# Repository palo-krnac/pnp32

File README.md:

# 🎯 **pnp32 Modular Motion Controller for openPNP**

High-performance, fully modular motion controller for advanced Pick & Place machines. Designed to seamlessly integrate with OpenPnP and support direct SPI-controlled stepper drivers for ultra-smooth and precise motion.

!!! danger "Work in Progress"
    This project is currently under active development.  
    Features and documentation may change frequently.  
    Use at your own discretion.

👉 [See pnp32 documentation page](https://pnp32.telemetry.digital)

---

## 🚀 **Key Features**

- ✅ **ESP32 based core** — powerful microcontroller with floating-point, high-speed I/O, and robust connectivity
- ✅ **Native SPI motion control** — supports TMC5160, TMC5130, PowerSTEP01, and L64xx drivers without STEP/DIR emulation
- ✅ **Flexible architecture** — single-board and multi-board configurations for scalable machine designs
- ✅ **CAN bus interface** — robust communication between multiple controllers or modular head units
- ✅ **RS485 interface** — control feeder modules or additional peripherals with industrial reliability
- ✅ **Integrated vacuum and air control** — including pressure/vacuum sensing and smart valve control
- ✅ **Advanced lighting and vision control** — supports multi-channel LED lighting, camera triggers, and auxiliary outputs
- ✅ **USB-to-Serial bridge** — direct communication with OpenPnP software

---

## 🧩 **Modifications & Configurations**

### 🔹 **Modification 1: Single Board Setup**

- All stepper motor drivers for all axes integrated on one board
- Centralized control logic with all communication interfaces (CAN, RS485, USB)
- Simplified wiring for smaller or simpler machines

### 🔹 **Modification 2: Dual Board Modular Setup**

#### 🟦 **Main Controller Board**

- Controls primary machine axes: X, Y, or duplicated X + single Y (up to 3 axes)
- Handles all communication interfaces (CAN, RS485, USB)
- Acts as the master motion controller

#### 🟩 **Head Controller Board**

- Mounted on the machine head(s), connected via CAN bus
- Controls additional axes: Z, A, B, C, D, E, F
- Supports air/vacuum control, pressure/vacuum sensing
- Controls head lighting, glue/paste dispensers
- Available in two variants:
  - 2-head version: for two nozzles
  - 4-head version: supports four nozzles or combination of nozzles & dispensers

---

## ⚙️ **G-code Configuration & Machine Parameters**

All key motion parameters and hardware configurations are set directly from OpenPnP via custom G-code commands. This enables easy tuning, calibration, and reconfiguration without modifying firmware or recompiling code.

### 💬 **Supported G-code Commands**

| G-code        | Description                                 | Example Usage                        | Documentation |
|---------------|---------------------------------------------|-------------------------------------|---------------|
| `M350`        | Set microstepping for each axis            | `M350 X16 Y16 Z32`                 | [RepRap M350](https://marlinfw.org/docs/gcode/M350.html) |
| `M906`        | Set motor current (mA) per axis           | `M906 X1000 Y1000 Z800`           | [RepRap M906](https://marlinfw.org/docs/gcode/M906.html) |
| `M92`         | Set steps per mm (axis scaling)           | `M92 X80 Y80 Z400`                | [RepRap M92](https://marlinfw.org/docs/gcode/M092.html) |
| `M211`        | Enable/disable software endstops          | `M211 S1`                          | [RepRap M211](https://marlinfw.org/docs/gcode/M211.html) |
| `M208`        | Set axis travel limits (soft limits)      | `M208 X0:300 Y0:250 Z0:150`      | [Duet3D M208](https://docs.duet3d.com/User_manual/Reference/Gcode#m208) |
| `M569`        | Configure driver direction inversion      | `M569 X0 Y1 Z0`                   | [Duet3D M569](https://docs.duet3d.com/User_manual/Reference/Gcode#m569) |
| `M912`        | Set driver sense resistor calibration     | `M912 X20 Y20 Z18`               | Custom command |
| `M913`        | Set dynamic current scaling %            | `M913 X70 Y70 Z80`              | [Duet3D M913](https://docs.duet3d.com/User_manual/Reference/Gcode#m913) |
| `M950`        | Configure pin assignments for outputs    | `M950 P1 S0`                     | [Duet3D M950](https://docs.duet3d.com/User_manual/Reference/Gcode#m950) |
| `M355`        | Control LED lighting intensity            | `M355 P1 S255`                  | [RepRap M355](https://marlinfw.org/docs/gcode/M355.html) |
| `M420`        | Enable bed leveling or machine compensation (if used) | `M420 S1`          | [RepRap M420](https://marlinfw.org/docs/gcode/M420.html) |

### 🛠 **Possible Additional Configurations**

- Set acceleration, max speed, and jerk per axis (future extension)
- Configure vacuum thresholds and pressure sensor calibration
- Assign specific CAN node IDs for multi-board setups
- Control glue/paste pump parameters (pulse lengths, flow rates)
- Define custom tool offsets and head calibration parameters

---

## 🛠 **Board Parameters**

| Parameter         | Value                                      |
|-------------------|--------------------------------------------|
| **MCU**           | ESP32                                      |
| **Motor Drivers** | SPI controlled: TMC5160, TMC5130, PowerSTEP01, L64xx |
| **Axes**          | Up to 12 axes total (depending on config) |
| **Feeders**       | Up to 63 feeders total (depending on config) |
| **Comm. Interfaces** | CAN bus, RS485, USB-Serial             |
| **Peripheral Control** | Air/vacuum valves, pressure sensors, lighting |
| **Voltage**       | 12–48 V supply for motors                |
| **Safety**        | E-stop input, software limits, watchdog  |

---

## 💻 **Software**

- Developed in **PlatformIO**
- Custom motion control firmware optimized for SPI-based drivers
- CAN bus stack for modular multi-board communication
- Feeder and peripheral control via RS485
- OpenPnP-compatible serial communication with dynamic G-code support

---

## 💡 **Highlights**

- Ultra-precise motion with direct register-level SPI control (no missed steps)
- Full machine configuration and tuning via standard G-code from OpenPnP
- Modular design ready for scalable, high-end Pick & Place machines
- Multi-head and multi-function ready: placement, glue dispensing, paste dispensing
- Designed for tinkerers, prosumers, and professional machine builders alike

---

## 📦 **Getting Started**

1️⃣ Clone this repository  
2️⃣ Install PlatformIO and dependencies  
3️⃣ Configure your hardware via G-code or `config.h` for base defaults  
4️⃣ Flash the firmware to your controller board  
5️⃣ Connect to OpenPnP and start tuning!

---

## 🛡 **License**

This project is open-source under the MIT License. Contributions and pull requests are warmly welcome!

---

## ❤️ **Credits & Inspiration**

Inspired by OpenPnP community, modern motion control concepts, and the open hardware spirit. Special thanks to Trinamic (TMC), STMicroelectronics (PowerSTEP01, L64xx), and the global DIY PnP community.

---

## ✨ **Screenshots & Diagrams**

*(Insert board design images, modular connection diagrams, example machine setups, head modules, etc.)*

---

### ✅ **Ready to go? Let's build next-level OpenPnP machines together!**
"""

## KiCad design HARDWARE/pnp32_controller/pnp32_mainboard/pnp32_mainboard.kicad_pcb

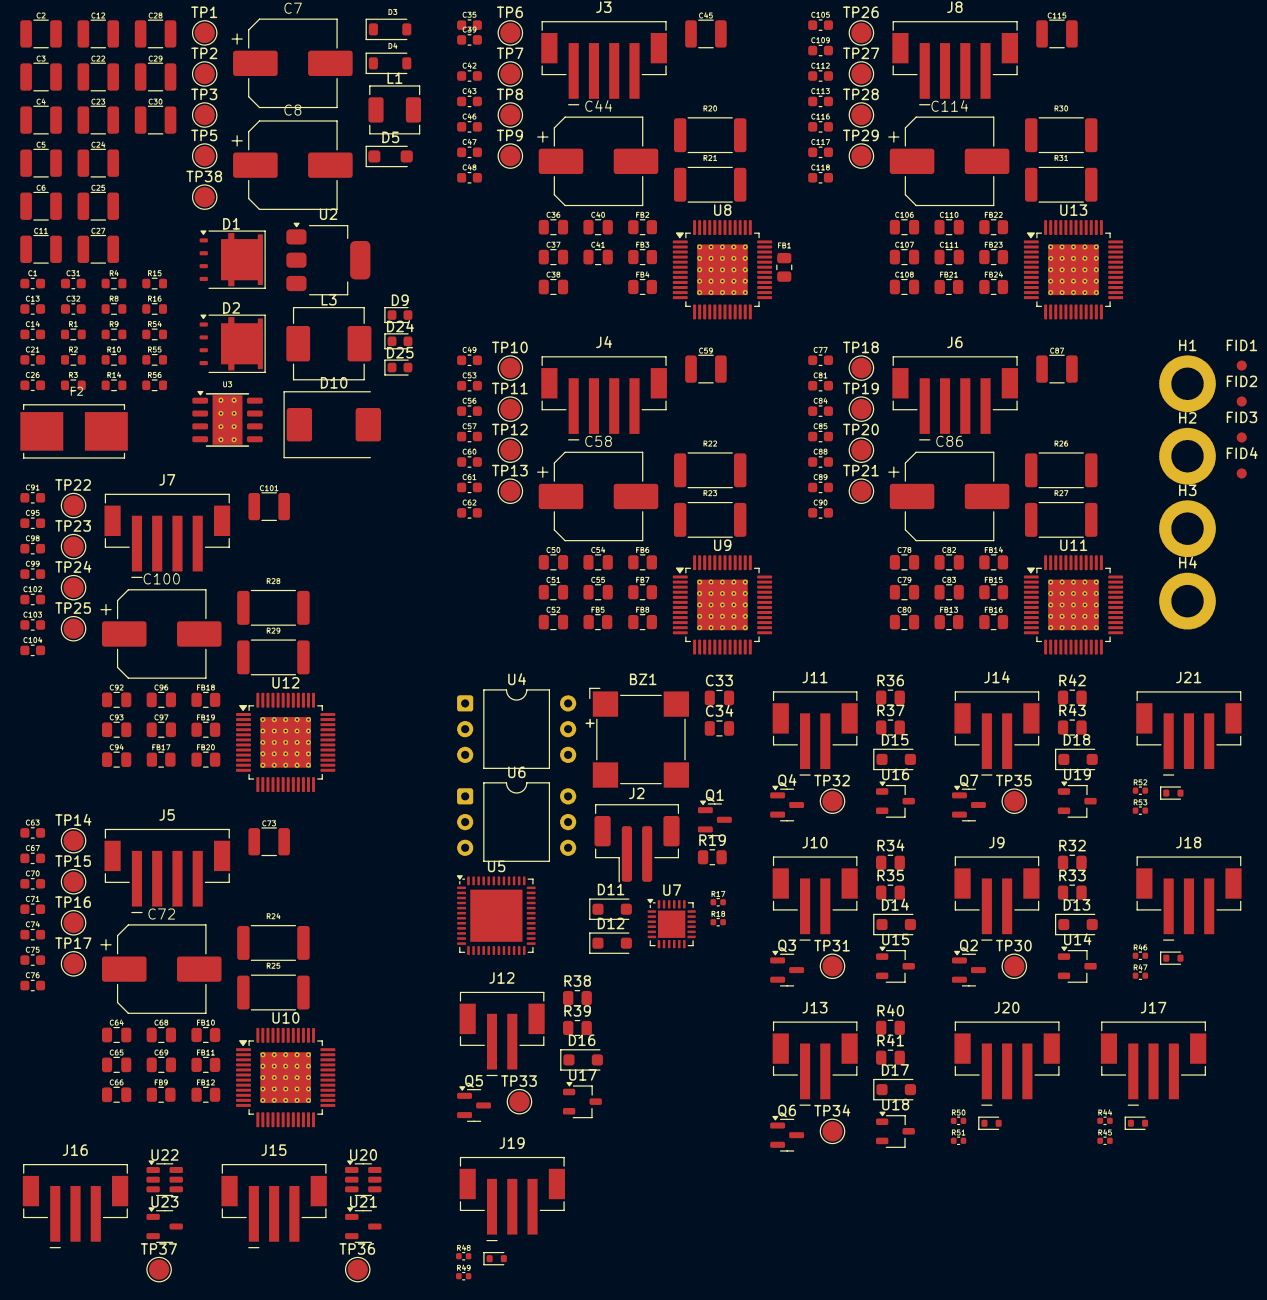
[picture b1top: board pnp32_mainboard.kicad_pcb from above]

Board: 2 copper layers, 304 parts (0 on the bottom side), 144 nets, no tracks yet.

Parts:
BZ1: Buzzer; MagneticBuzzer_CUI_CMT-8504-100-SMT
C1, C13, C14, C21, C26, C42, C43, C46, C47, C48, C56, C57, C60, C61, C62, C70, C71, C74, C75, C76, C84, C85, C88, C89, C90, C98, C99, C102, C103, C104, C112, C113, C116, C117, C118: 100nF; C_0603
C2, C3, C4, C5, C6, C11, C12, C22, C23, C24, C25, C45, C59, C73, C87, C101, C115: 10uF; C_1210
C7, C8, C44, C58, C72, C86, C100, C114: 100uF/50V; CP_Elec_8x10.5
C27, C28, C29, C30: 22uF; C_1210
C31: 47pF; C_0603
C32: 4.7nF; C_0603
C33, C34: 100n; C_0805_2012Metric
C35, C49, C63, C77, C91, C105: 4.7uF; C_0603
C36, C37, C38, C40, C41, C50, C51, C52, C54, C55, C64, C65, C66, C68, C69, C78, C79, C80, C82, C83, C92, C93, C94, C96, C97, C106, C107, C108, C110, C111: 470pF; C_0805
C39, C53, C67, C81, C95, C109: 22nF; C_0603
D1, D2: SQJ479EP-T1_GE3; PowerPAK_SO-8L_Single
D3, D4: BZT52C16; SOD-123
D5: SMF28A; SOD-123FL
D9, D24, D25: GREEN; LED_0603_1608Metric
D10: B560C; SMC
D11, D12, D13, D14, D15, D16, D17, D18: SM4007; D_SOD-123F
D19, D20, D21, D22, D23: LESD5D5.0CT1G; SOD-523
F2: 01550900M; Fuseholder_Littelfuse_Nano2_154x
FB1, FB2, FB3, FB4, FB5, FB6, FB7, FB8, FB9, FB10, FB11, FB12, FB13, FB14, FB15, FB16, FB17, FB18, FB19, FB20, FB21, FB22, FB23, FB24: FerriteBead; R_0805
FID1, FID2, FID3, FID4: Fiducial; Fiducial_1mm_Mask2mm
H1, H2, H3, H4: MountingHole_Pad; MountingHole_3.2mm_M3_DIN965_Pad
J2: FAN; JST_PH_B2B-PH-SM4-TB_1x02-1MP_P2.00mm_Vertical
J3, J4, J5, J6, J7, J8: Conn_01x04_Pin; WE_620304124022
J9, J10, J11, J12, J13, J14: Conn_01x02_Pin; WE_620302124022
J15, J16, J17, J18, J19, J20, J21: Conn_01x03_Pin; WE_620303124022
L1: 2.2uH; L_Sunlord_MWSA0402S
L3: 8.2uH; L_Changjiang_FXL0630
Q1, Q2, Q3, Q4, Q5, Q6, Q7: AO3400A; SOT-23
R1, R2, R9: 4.7kΩ; R_0603
R3, R4, R10: 10kΩ; R_0603
R8: 1kΩ; R_0603
R14: 53.6kΩ; R_0603
R15: 16.9kΩ; R_0603
R16: 243kΩ; R_0603
R17, R18: 4.7kΩ; R_0402
R19, R32, R34, R36, R38, R40, R42: 1k; R_0805_2012Metric
R20, R21, R22, R23, R24, R25, R26, R27, R28, R29, R30, R31: 120mΩ; R_2512
R33, R35, R37, R39, R41, R43: 10k; R_0805_2012Metric
R44, R46, R48, R50, R52: 10kΩ; R_0402
R45, R47, R49, R51, R53: 1kΩ; R_0402
R54: 442kΩ; R_0603
R55: 90.9kΩ; R_0603
R56: 10.2kΩ; R_0603
TP1, TP2, TP3, TP5, TP6, TP7, TP8, TP9, TP10, TP11, TP12, TP13, TP14, TP15, TP16, TP17, TP18, TP19, TP20, TP21, TP22, TP23, TP24, TP25, TP26, TP27, TP28, TP29, TP30, TP31, TP32, TP33, TP34, TP35, TP36, TP37, TP38: TestPoint; TestPoint_Pad_D2.0mm
U2: AMS1117-3.3; SOT-223
U3: TPS54560BDDAR; Texas_HSOP-8-1EP_3.9x4.9mm_P1.27mm_ThermalVias
U4, U6: XGZP6857D; DIP-6_W10.16mm
U5: ESP32-PICO-V3; QFN-48-1EP_7x7mm_P0.5mm_EP5.15x5.15mm
U7: FE1.1S-BQFN24B; WQFN-24-1EP_4x4mm_P0.5mm_EP2.7x2.7mm
U8, U9, U10, U11, U12, U13: TMC5130A-TA; TQFP-48-1EP_7x7mm_P0.5mm_EP5x5mm_ThermalVias
U14, U15, U16, U17, U18, U19: PESD24BS3; TSOT-23
U20, U22: SN74LVC2G34; SOT-23-6
U21, U23: PESD5V2S2UT; SOT-23-3

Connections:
+3.3V: C11.1, C13.1, C33.1, C34.1, C48.1, C62.1, C76.1, C90.1, C104.1, C118.1, R8.1, R17.1, R18.1, R44.1, R46.1, R48.1, R50.1, R52.1, TP5.1, U2.2 (Vout), U2.4 (Vout), U4.2 (VDD), U5.1 (VDDA), U5.3 (VDD3P3), U5.4 (VDD3P3), U5.19 (VDD3P3_RTC), U5.26 (VDD_SDIO), U5.37 (VDD3P3_CPU), U5.43 (VDDA), U5.46 (VDDA), U6.2 (VDD), U8.10 (VCC_IO), U9.10 (VCC_IO), U10.10 (VCC_IO), U11.10 (VCC_IO), U12.10 (VCC_IO), U13.10 (VCC_IO)
+5V: BZ1.1 (-), C12.1, C14.1, C27.1, C28.1, C29.1, C30.1, D11.1 (K), D12.1 (K), J2.1, J15.1, J16.1, J17.1, J18.1, J19.1, J20.1, J21.1, L3.2, R9.1, R14.1, TP38.1, U2.3 (Vin), U20.5 (VCC), U22.5 (VCC)
/A-driver/A1: C79.1, FB13.2, J6.3, TP18.1
/A-driver/A2: C80.2, FB14.2, J6.4, TP19.1
/A-driver/B1: C82.1, FB15.2, J6.2, TP20.1
/A-driver/B2: C83.2, FB16.2, J6.1, TP21.1
/A-driver/CPI: C81.2, U11.37 (CPI)
/A-driver/CPO: C81.1, U11.35 (CP0)
/A-driver/SPI_CLK: U5.34 (GPIO5), U8.4 (SCK_CFG2), U9.4 (SCK_CFG2), U10.4 (SCK_CFG2), U11.4 (SCK_CFG2), U12.4 (SCK_CFG2), U13.4 (SCK_CFG2)
/A-driver/SPI_CS: U5.39 (GPIO22), U11.3 (~CS_CFG3)
/A-driver/SPI_MISO: U5.22 (GPIO2/ADC2_CH2), U8.7 (SDO_NAO_CFG0), U9.7 (SDO_NAO_CFG0), U10.7 (SDO_NAO_CFG0), U11.7 (SDO_NAO_CFG0), U12.7 (SDO_NAO_CFG0), U13.7 (SDO_NAO_CFG0)
/A-driver/SPI_MOSI: U5.24 (GPIO4/ADC2_CH0), U8.5 (SDI_NAI_CFG1), U9.5 (SDI_NAI_CFG1), U10.5 (SDI_NAI_CFG1), U11.5 (SDI_NAI_CFG1), U12.5 (SDI_NAI_CFG1), U13.5 (SDI_NAI_CFG1)
/B-driver/A1: C93.1, FB17.2, J7.3, TP22.1
/B-driver/A2: C94.2, FB18.2, J7.4, TP23.1
/B-driver/B1: C96.1, FB19.2, J7.2, TP24.1
/B-driver/B2: C97.2, FB20.2, J7.1, TP25.1
/B-driver/CPI: C95.2, U12.37 (CPI)
/B-driver/CPO: C95.1, U12.35 (CP0)
/B-driver/SPI_CS: U5.14 (GPIO25/ADC2_CH8/DAC_1), U12.3 (~CS_CFG3)
/C-driver/A1: C107.1, FB21.2, J8.3, TP26.1
/C-driver/A2: C108.2, FB22.2, J8.4, TP27.1
/C-driver/B1: C110.1, FB23.2, J8.2, TP28.1
/C-driver/B2: C111.2, FB24.2, J8.1, TP29.1
/C-driver/CPI: C109.2, U13.37 (CPI)
/C-driver/CPO: C109.1, U13.35 (CP0)
/C-driver/SPI_CS: U5.15 (GPIO26/ADC2_CH9/DAC_2), U13.3 (~CS_CFG3)
/CPU/AIR1: R38.2, U5.6 (SENSOR_CAPP/GPIO37/ADC1_CH1)
/CPU/AIR2: R40.2, U5.7 (SENSOR_CAPN/GPIO38/ADC1_CH2)
/CPU/AIR_PUMP: R42.2, U5.8 (SENSOR_VN/GPIO39/ADC1_CH3)
/CPU/BUZZER: R19.1, U5.21 (MTDO/GPIO15/ADC2_CH3)
/CPU/I2C_SCL: R18.2, U4.5 (SCL), U5.32 (SD_DATA_0/GPIO7), U6.5 (SCL)
/CPU/I2C_SDA: R17.2, U4.4 (SDA), U5.31 (SD_CLK/GPIO6), U6.4 (SDA)
/CPU/SPI_CS_X: U5.38 (GPIO19), U8.3 (~CS_CFG3)
/CPU/SPI_CS_Y: U5.27 (GPIO20), U9.3 (~CS_CFG3)
/CPU/SPI_CS_Z: U5.42 (GPIO21), U10.3 (~CS_CFG3)
/CPU/VAC1: R32.2, U5.10 (VDET_1/GPIO34/ADC1_CH6)
/CPU/VAC2: R34.2, U5.11 (VDET_2/GPIO35/ADC1_CH7)
/CPU/VAC_PUMP: R36.2, U5.5 (SENSOR_VP/GPIO36/ADC1_CH0)
/CPU/WLED_BOTTOM: U5.28 (SD_DATA_2/GPIO9), U20.1 (1A)
/CPU/WLED_TOP: U5.33 (SD_DATA_1/GPIO8), U22.1 (1A)
/PSU/VIN: C2.1, D1.3 (D), D5.1 (A1), F2.2, TP1.1
/X-driver/A1: C37.1, FB1.2, J3.3, TP6.1
/X-driver/A2: C38.2, FB2.2, J3.4, TP7.1
/X-driver/B1: C40.1, FB3.2, J3.2, TP8.1
/X-driver/B2: C41.2, FB4.2, J3.1, TP9.1
/X-driver/CPI: C39.2, U8.37 (CPI)
/X-driver/CPO: C39.1, U8.35 (CP0)
/Y-driver/A1: C51.1, FB5.2, J4.3, TP10.1
/Y-driver/A2: C52.2, FB6.2, J4.4, TP11.1
/Y-driver/B1: C54.1, FB7.2, J4.2, TP12.1
/Y-driver/B2: C55.2, FB8.2, J4.1, TP13.1
/Y-driver/CPI: C53.2, U9.37 (CPI)
/Y-driver/CPO: C53.1, U9.35 (CP0)
/Z-driver/A1: C65.1, FB9.2, J5.3, TP14.1
/Z-driver/A2: C66.2, FB10.2, J5.4, TP15.1
/Z-driver/B1: C68.1, FB11.2, J5.2, TP16.1
/Z-driver/B2: C69.2, FB12.2, J5.1, TP17.1
/Z-driver/CPI: C67.2, U10.37 (CPI)
/Z-driver/CPO: C67.1, U10.35 (CP0)
GND: C2.2, C3.2, C4.2, C5.2, C6.2, C7.2, C8.2, C11.2, C12.2, C13.2, C14.2, C22.2, C23.2, C24.2, C25.2, C26.2, C27.2, C28.2, C29.2, C30.2, C31.2, C32.2, C33.2, C34.2, C35.2, C36.2, C37.2, C38.1, C40.2, C41.1, C42.2, C43.2, C44.2, C45.2, C46.2, C47.2, C48.2, C49.2, C50.2, C51.2, C52.1, C54.2, C55.1, C56.2, C57.2, C58.2, C59.2, C60.2, C61.2, C62.2, C63.2, C64.2, C65.2, C66.1, C68.2, C69.1, C70.2, C71.2, C72.2, C73.2, C74.2, C75.2, C76.2, C77.2, C78.2, C79.2, C80.1, C82.2, C83.1, C84.2, C85.2, C86.2, C87.2, C88.2, C89.2, C90.2, C91.2, C92.2, C93.2, C94.1, C96.2, C97.1, C98.2, C99.2, C100.2, C101.2, C102.2, C103.2, C104.2, C105.2, C106.2, C107.2, C108.1, C110.2, C111.1, C112.2, C113.2, C114.2, C115.2, C116.2, C117.2, C118.2, D5.2 (A2), D9.1 (K), D10.2 (A2), D12.2 (A), D19.1 (A1), D20.1 (A1), D21.1 (A1), D22.1 (A1), D23.1 (A1), D24.1 (K), D25.1 (K), H1.1, H2.1, H3.1, H4.1, J2.2, J2.MP (MountPin), J15.3, J16.3, J17.3, J18.3, J19.3, J20.3, J21.3, Q1.2 (S), Q2.2 (S), Q3.2 (S), Q4.2 (S), Q5.2 (S), Q6.2 (S), Q7.2 (S), R3.2, R4.2, R16.2, R20.2, R21.2, R22.2, R23.2, R24.2, R25.2, R26.2, R27.2, R28.2, R29.2, R30.2, R31.2, R33.1, R35.1, R37.1, R39.1, R41.1, R43.1, R55.2, R56.2, TP3.1, U2.1 (GND), U3.7 (GND), U3.9 (GND), U4.6 (GND), U5.49 (GND), U6.6 (GND), U8.1 (TST_MODE), U8.2 (CLK), U8.13 (GNDP), U8.24 (ENCB_DCEN_CFG4), U8.48 (GNDP), U9.1 (TST_MODE), U9.2 (CLK), U9.13 (GNDP), U9.24 (ENCB_DCEN_CFG4), U9.48 (GNDP), U10.1 (TST_MODE), U10.2 (CLK), U10.13 (GNDP), U10.24 (ENCB_DCEN_CFG4), U10.48 (GNDP), U11.1 (TST_MODE), U11.2 (CLK), U11.13 (GNDP), U11.24 (ENCB_DCEN_CFG4), U11.48 (GNDP), U12.1 (TST_MODE), U12.2 (CLK), U12.13 (GNDP), U12.24 (ENCB_DCEN_CFG4), U12.48 (GNDP), U13.1 (TST_MODE), U13.2 (CLK), U13.13 (GNDP), U13.24 (ENCB_DCEN_CFG4), U13.48 (GNDP), U14.3, U15.3, U16.3, U17.3, U18.3, U19.3, U20.2 (GND), U21.3, U22.2 (GND), U23.3
unnamed: BZ1.2 (+), D11.2 (A), Q1.3 (D)
unnamed: C32.1, R15.2
unnamed: D1.2 (G), D3.2 (A), R1.2, R3.1
unnamed: C1.1, D1.1 (S), D2.1 (S), D3.1 (K), D4.1 (K), R1.1, R2.1
unnamed: C3.1, C4.1, D2.3 (D), L1.1
unnamed: C1.2, D2.2 (G), D4.2 (A), R2.2, R4.1
unnamed: D9.2 (A), R8.2
unnamed: C21.2, D10.1 (A1), L3.1, U3.8 (SW)
unnamed: D13.2 (A), J9.2, Q2.3 (D), TP30.1, U14.2
unnamed: D14.2 (A), J10.2, Q3.3 (D), TP31.1, U15.2
unnamed: D15.2 (A), J11.2, Q4.3 (D), TP32.1, U16.2
unnamed: D16.2 (A), J12.2, Q5.3 (D), TP33.1, U17.2
unnamed: D17.2 (A), J13.2, Q6.3 (D), TP34.1, U18.2
unnamed: D18.2 (A), J14.2, Q7.3 (D), TP35.1, U19.2
unnamed: D19.2 (A2), J17.2, R44.2, R45.2
unnamed: D20.2 (A2), J18.2, R46.2, R47.2
unnamed: D21.2 (A2), J19.2, R48.2, R49.2
unnamed: D22.2 (A2), J20.2, R50.2, R51.2
unnamed: D23.2 (A2), J21.2, R52.2, R53.2
unnamed: D24.2 (A), R9.2
unnamed: D25.2 (A), R10.2
unnamed: J15.2, TP36.1, U20.6 (1Y), U21.1
unnamed: J16.2, TP37.1, U22.6 (1Y), U23.1
unnamed: Q1.1 (G), R19.2
unnamed: Q2.1 (G), R32.1, R33.2
unnamed: Q3.1 (G), R34.1, R35.2
unnamed: Q4.1 (G), R36.1, R37.2
unnamed: Q5.1 (G), R38.1, R39.2
unnamed: Q6.1 (G), R40.1, R41.2
unnamed: Q7.1 (G), R42.1, R43.2
unnamed: C21.1, U3.1 (BOOT)
unnamed: C31.1, R15.1, U3.6 (COMP)
unnamed: R54.2, R55.1, U3.3 (EN)
unnamed: R14.2, R56.1, U3.5 (FB)
unnamed: R16.1, U3.4 (RT/CLK)
unnamed: C35.1, U8.33 (5VOUT)
unnamed: C43.1, R21.1, U8.44 (BRA)
unnamed: C42.1, R20.1, U8.17 (BRB)
unnamed: FB1.1, U8.46 (OA1)
unnamed: FB2.1, U8.42 (OA2)
unnamed: FB3.1, U8.15 (OB1)
unnamed: FB4.1, U8.19 (OB2)
unnamed: C36.1, U8.34 (VCC)
unnamed: C49.1, U9.33 (5VOUT)
unnamed: C57.1, R23.1, U9.44 (BRA)
unnamed: C56.1, R22.1, U9.17 (BRB)
unnamed: FB5.1, U9.46 (OA1)
unnamed: FB6.1, U9.42 (OA2)
unnamed: FB7.1, U9.15 (OB1)
unnamed: FB8.1, U9.19 (OB2)
unnamed: C50.1, U9.34 (VCC)
unnamed: C63.1, U10.33 (5VOUT)
unnamed: C71.1, R25.1, U10.44 (BRA)
unnamed: C70.1, R24.1, U10.17 (BRB)
unnamed: FB9.1, U10.46 (OA1)
unnamed: FB10.1, U10.42 (OA2)
unnamed: FB11.1, U10.15 (OB1)
unnamed: FB12.1, U10.19 (OB2)
unnamed: C64.1, U10.34 (VCC)
unnamed: C77.1, U11.33 (5VOUT)
unnamed: C85.1, R27.1, U11.44 (BRA)
unnamed: C84.1, R26.1, U11.17 (BRB)
unnamed: FB13.1, U11.46 (OA1)
unnamed: FB14.1, U11.42 (OA2)
unnamed: FB15.1, U11.15 (OB1)
unnamed: FB16.1, U11.19 (OB2)
unnamed: C78.1, U11.34 (VCC)
unnamed: C91.1, U12.33 (5VOUT)
unnamed: C99.1, R29.1, U12.44 (BRA)
unnamed: C98.1, R28.1, U12.17 (BRB)
unnamed: FB17.1, U12.46 (OA1)
unnamed: FB18.1, U12.42 (OA2)
unnamed: FB19.1, U12.15 (OB1)
unnamed: FB20.1, U12.19 (OB2)
unnamed: C92.1, U12.34 (VCC)
unnamed: C105.1, U13.33 (5VOUT)
unnamed: C113.1, R31.1, U13.44 (BRA)
unnamed: C112.1, R30.1, U13.17 (BRB)
unnamed: FB21.1, U13.46 (OA1)
unnamed: FB22.1, U13.42 (OA2)
unnamed: FB23.1, U13.15 (OB1)
unnamed: FB24.1, U13.19 (OB2)
unnamed: C106.1, U13.34 (VCC)
VDC: C5.1, C6.1, C7.1, C8.1, C22.1, C23.1, C24.1, C25.1, C26.1, C44.1, C45.1, C58.1, C59.1, C72.1, C73.1, C86.1, C87.1, C100.1, C101.1, C114.1, C115.1, D13.1 (K), D14.1 (K), D15.1 (K), D16.1 (K), D17.1 (K), D18.1 (K), J9.1, J10.1, J11.1, J12.1, J13.1, J14.1, L1.2, R10.1, R54.1, TP2.1, U3.2 (VIN), U8.21 (VS), U9.21 (VS), U10.21 (VS), U11.21 (VS), U12.21 (VS), U13.21 (VS), U14.1, U15.1, U16.1, U17.1, U18.1, U19.1

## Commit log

2025-07-05 first_update
2025-07-05 upload
2025-07-05 update site
2025-07-20 Deployed bf660e3 with MkDocs version: 1.6.1
2025-07-20 Create CNAME
2025-07-20 Deployed bd61da5 with MkDocs version: 1.6.1
2025-07-20 update docs
2025-07-20 Deployed 1133394 with MkDocs version: 1.6.1
2025-07-20 Deployed ff86ace with MkDocs version: 1.6.1
2025-07-20 Deployed 1eeedd6 with MkDocs version: 1.6.1
2025-07-20 Pridany CNAME pre vlastnu domenu
2025-07-20 Deployed 758396b with MkDocs version: 1.6.1
2025-07-20 Deployed f115c7f with MkDocs version: 1.6.1
2025-07-20 deploy
2025-07-20 Deployed 3c40719 with MkDocs version: 1.6.1
2025-07-20 Deployed e7203a0 with MkDocs version: 1.6.1
2025-07-20 Deployed dad19c6 with MkDocs version: 1.6.1
2025-07-20 Deployed 0e86a5f with MkDocs version: 1.6.1
2025-07-20 Deployed 3465994 with MkDocs version: 1.6.1
2025-07-24 update.docs
2025-07-24 Deployed dfdb985 with MkDocs version: 1.6.1
2025-07-25 update_firmware
2025-07-29 update firmware
2025-07-31 Deployed 14b69a2 with MkDocs version: 1.6.1
2025-08-02 update_docs
2025-08-02 Deployed 4db1f41 with MkDocs version: 1.6.1
2025-09-02 test
2025-09-04 update_PSU
